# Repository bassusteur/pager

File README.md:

This project is what i think an ideal portable pager would be like, powered by a risc-v core inside the ESP32-C6 on-board, it features a pretty standard interface for a pager: except for the 
exceptionally larger LCD, it has 4 buttons for selecting and writing text.  
Communication is made possible through various methods such as zigbee or wifi, the neat part is the Serial port which could allow for fun tinkering with computers and embedded devices.
Portability wise i have added an 18650 battery pack and all the circuitry necessary to make this an off-grid device.

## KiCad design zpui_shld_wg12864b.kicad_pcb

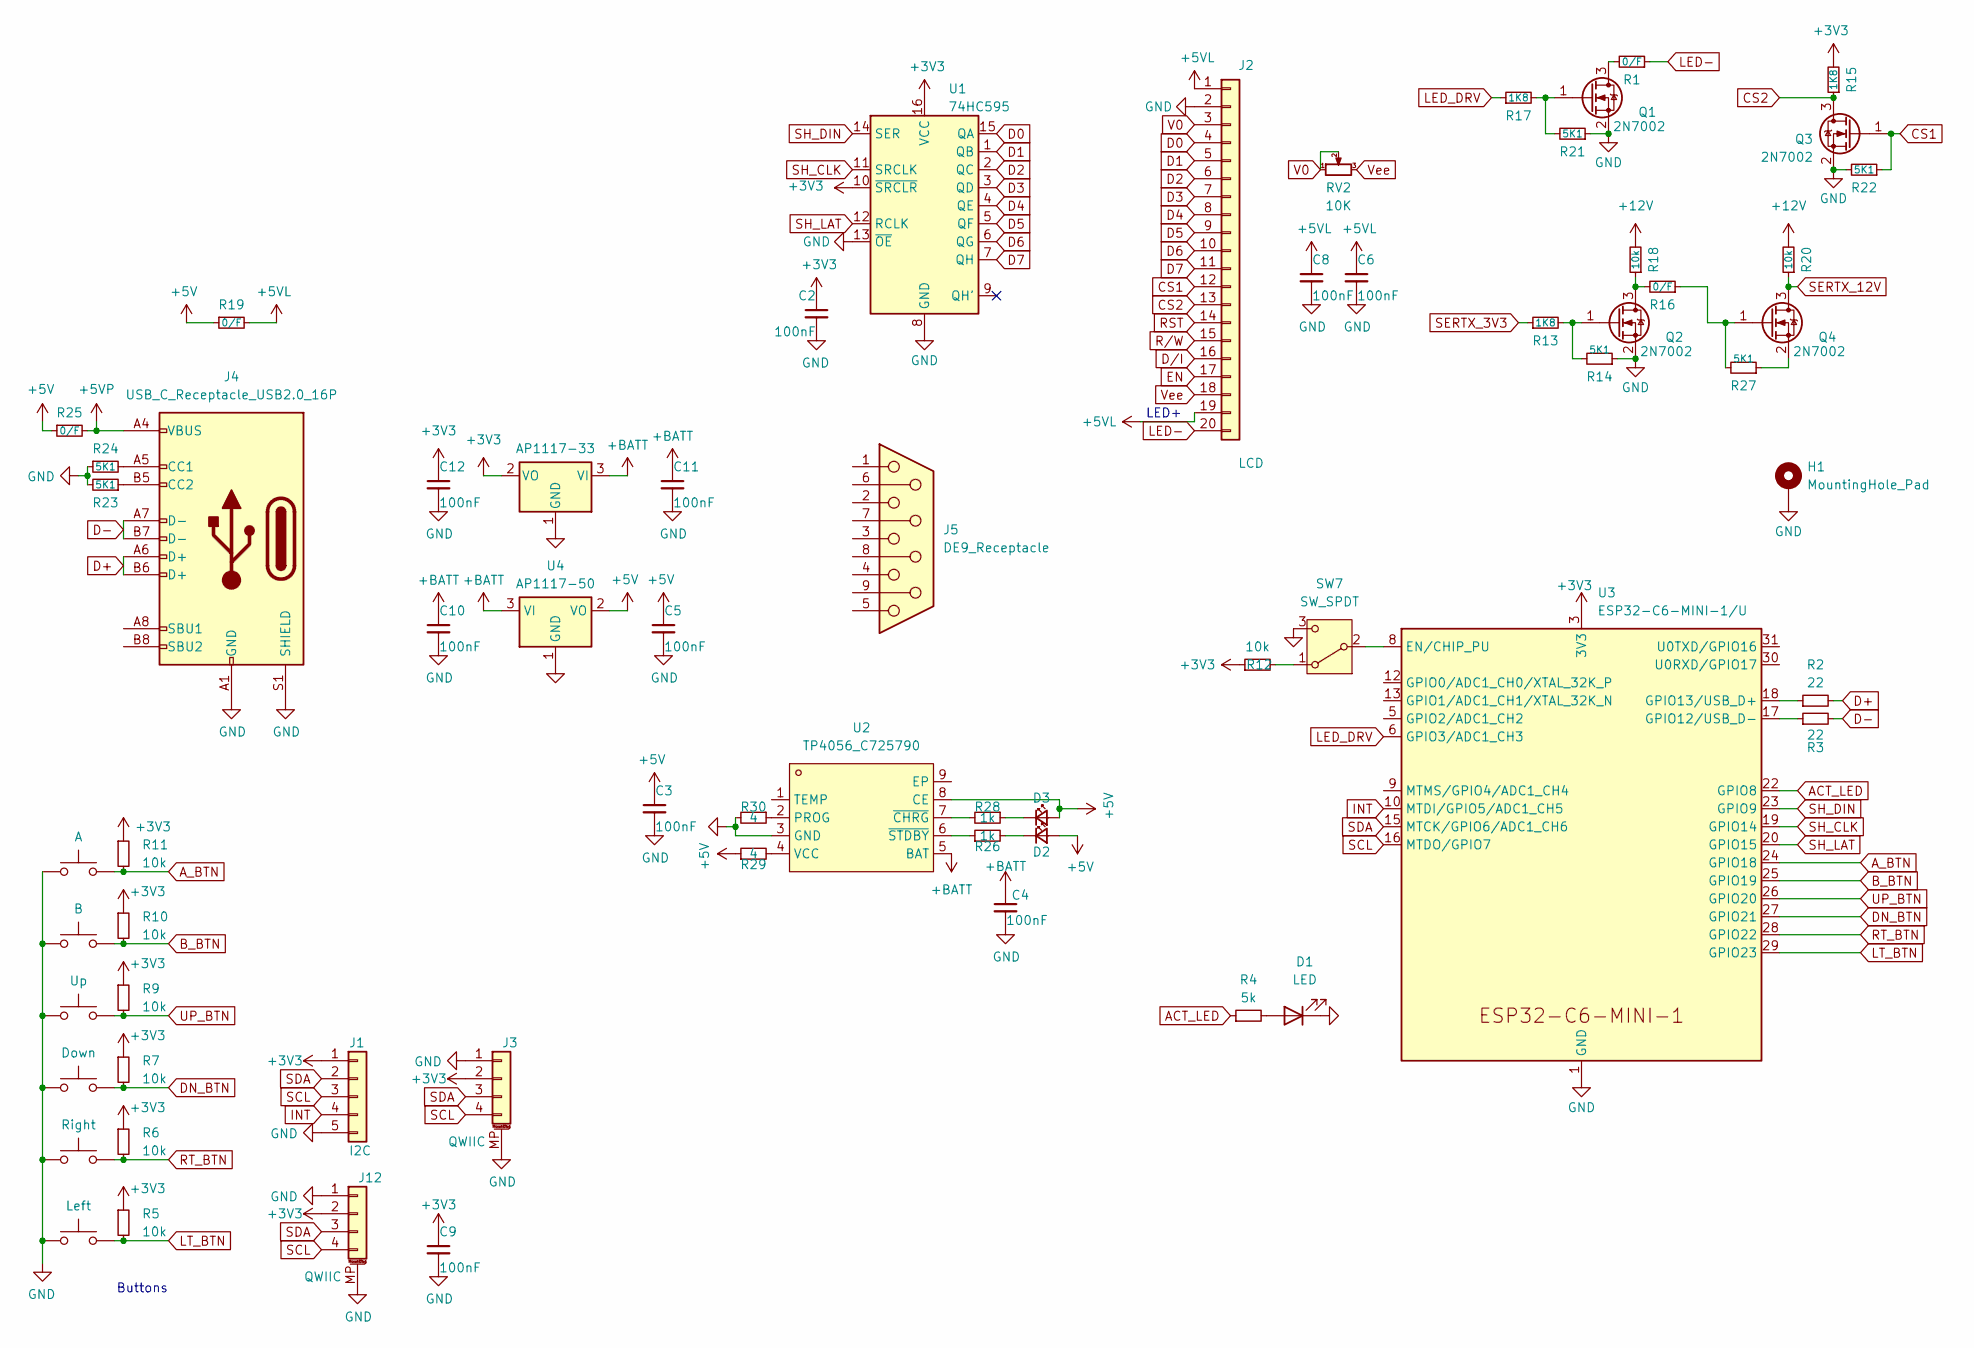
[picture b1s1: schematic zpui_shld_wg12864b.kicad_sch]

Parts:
C2, C3, C4, C5, C6, C8, C9, C10, C11, C12: 100nF; C_0603_1608Metric
D1: LED; LED_0603_1608Metric
D2, D3: LED_Small; LED_0603_1608Metric
H1: MountingHole_Pad; MountingHole_3mm_Pad
J1: I2C; PinHeader_1x05_P2.54mm_Vertical
J2: LCD; PinHeader_1x20_P2.54mm_Vertical
J3, J12: QWIIC; JST_SH_SM04B-SRSS-TB_1x04-1MP_P1.00mm_Horizontal
J4: USB_C_Receptacle_USB2.0_16P; USB_C_Receptacle_HRO_TYPE-C-31-M-12
J5: DE9_Receptacle
Q1, Q2, Q3, Q4: 2N7002; SOT-23
R1, R16, R19, R25: 0/F; R_0805_2012Metric
R2, R3: 22; R_0603_1608Metric
R4: 5k; R_0603_1608Metric
R5, R6, R7, R9, R10, R11, R18, R20: 10k; R_0603_1608Metric
R12: 10k
R13, R15, R17: 1K8; R_0603_1608Metric
R14, R21, R22, R23, R24, R27: 5K1; R_0603_1608Metric
R26, R28: 1k; R_0603_1608Metric
R29, R30: 4; R_0603_1608Metric
RV2: 10K; Potentiometer_Bourns_3314J_Vertical
SW1: A; SW_SPST_PTS645; LCSC Part # C285456
SW2: B; SW_SPST_PTS645; mpn REQUIRED https://www.lcsc.com/product-d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; LCSC Part # C285456
SW3: Up; SW_SPST_PTS645; mpn REQUIRED https://www.lcsc.com/product-d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; LCSC Part # C285456
SW4: Down; SW_SPST_PTS645; mpn REQUIRED https://www.lcsc.com/product-d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; LCSC Part # C285456
SW5: Right; SW_SPST_PTS645; mpn REQUIRED https://www.lcsc.com/product-d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; LCSC Part # C285456
SW6: Left; SW_SPST_PTS645; mpn REQUIRED https://www.lcsc.com/product-d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; LCSC Part # C285456
SW7: SW_SPDT
U1: 74HC595; SO-16_3.9x9.9mm_P1.27mm
U2: TP4056_C725790; ESOP-8_L4.9-W3.9-P1.27-LS6.0-BL-EP; LCSC Part C725790
U3: ESP32-C6-MINI-1/U; ESP32-C6-MINI-1
U4: AP1117-50; SOT-223-3_TabPin2
U5: AP1117-33; SOT-223-3_TabPin2

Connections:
+3V3: C2.1, C9.1, C12.1, J1.1, J3.2, J12.2, R5.1, R6.1, R7.1, R9.1, R10.1, R11.1, R12.1, R15.2, U1.10 (~SRCLR), U1.16 (VCC), U3.3 (3V3), U5.2 (VO)
+5V: C3.1, C5.1, D2.2 (A), D3.2 (A), R19.1, R25.1, R29.1, U2.8 (CE), U4.2 (VO)
+5VL: C6.1, C8.1, J2.1, J2.19, R19.2
+5VP: J4.A4 (VBUS), J4.A9 (VBUS), J4.B4 (VBUS), J4.B9 (VBUS), R25.2
+12V: R18.2, R20.2
+BATT: C4.1, C10.1, C11.1, U2.5 (BAT), U4.3 (VI), U5.3 (VI)
ACT_LED: R4.1, U3.22 (GPIO8)
A_BTN: R11.2, SW1.1, U3.24 (GPIO18)
B_BTN: R10.2, SW2.1, U3.25 (GPIO19)
CS1: J2.12, Q3.1 (G), R22.1
CS2: J2.13, Q3.3 (D), R15.1
D0: J2.4, U1.15 (QA)
D1: J2.5, U1.1 (QB)
D2: J2.6, U1.2 (QC)
D3: J2.7, U1.3 (QD)
D4: J2.8, U1.4 (QE)
D5: J2.9, U1.5 (QF)
D6: J2.10, U1.6 (QG)
D7: J2.11, U1.7 (QH)
D+: J4.A6 (D+), J4.B6 (D+), R2.2
D-: J4.A7 (D-), J4.B7 (D-), R3.2
DN_BTN: R7.2, SW4.1, U3.27 (GPIO21)
D/I: J2.16
EN: J2.17
GND: C2.2, C3.2, C4.2, C5.2, C6.2, C8.2, C9.2, C10.2, C11.2, C12.2, D1.1 (K), H1.1, J1.5, J2.2, J3.1, J3.MP (MountPin), J4.A1 (GND), J4.A12 (GND), J4.B1 (GND), J4.B12 (GND), J4.S1 (SHIELD), J12.1, J12.MP (MountPin), Q1.2 (S), Q2.2 (S), Q3.2 (S), R14.1, R21.1, R22.2, R23.2, R24.1, R30.2, SW1.2, SW2.2, SW3.2, SW4.2, SW5.2, SW6.2, SW7.3 (C), U1.8 (GND), U1.13 (~OE), U2.3 (GND), U3.1 (GND), U3.2 (GND), U3.11 (GND), U3.14 (GND), U3.36 (GND), U3.37 (GND), U3.38 (GND), U3.39 (GND), U3.40 (GND), U3.41 (GND), U3.42 (GND), U3.43 (GND), U3.44 (GND), U3.45 (GND), U3.46 (GND), U3.47 (GND), U3.48 (GND), U3.49 (GND), U3.50 (GND), U3.51 (GND), U3.52 (GND), U3.53 (GND), U4.1 (GND), U5.1 (GND)
INT: J1.4, U3.10 (MTDI/GPIO5/ADC1_CH5)
LED-: J2.20, R1.1
LED_DRV: R17.1, U3.6 (GPIO3/ADC1_CH3)
LT_BTN: R5.2, SW6.1, U3.29 (GPIO23)
unnamed: D1.2 (A), R4.2
unnamed: D2.1 (K), R26.2
unnamed: D3.1 (K), R28.1
unnamed: J4.A5 (CC1), R24.2
unnamed: J4.B5 (CC2), R23.1
unnamed: Q1.3 (D), R1.2
unnamed: Q1.1 (G), R17.2, R21.2
unnamed: Q2.3 (D), R16.2, R18.1
unnamed: Q2.1 (G), R13.2, R14.2
unnamed: Q4.1 (G), R16.1, R27.2
unnamed: Q4.2 (S), R27.1
unnamed: R12.2, SW7.1 (A)
unnamed: SW7.2 (B), U3.8 (EN/CHIP_PU)
unnamed: R30.1, U2.2 (PROG)
unnamed: R29.2, U2.4 (VCC)
unnamed: R28.2, U2.7 (~CHRG)
unnamed: R26.1, U2.6 (~STDBY)
unnamed: R3.1, U3.17 (GPIO12/USB_D-)
unnamed: R2.1, U3.18 (GPIO13/USB_D+)
RST: J2.14
RT_BTN: R6.2, SW5.1, U3.28 (GPIO22)
R/W: J2.15
SCL: J1.3, J3.4, J12.4, U3.16 (MTDO/GPIO7)
SDA: J1.2, J3.3, J12.3, U3.15 (MTCK/GPIO6/ADC1_CH6)
SERTX_3V3: R13.1
SERTX_12V: Q4.3 (D), R20.1
SH_CLK: U1.11 (SRCLK), U3.19 (GPIO14)
SH_DIN: U1.14 (SER), U3.23 (GPIO9)
SH_LAT: U1.12 (RCLK), U3.20 (GPIO15)
UP_BTN: R9.2, SW3.1, U3.26 (GPIO20)
V0: J2.3, RV2.1, RV2.2
Vee: J2.18, RV2.3

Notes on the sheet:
Buttons
LED+

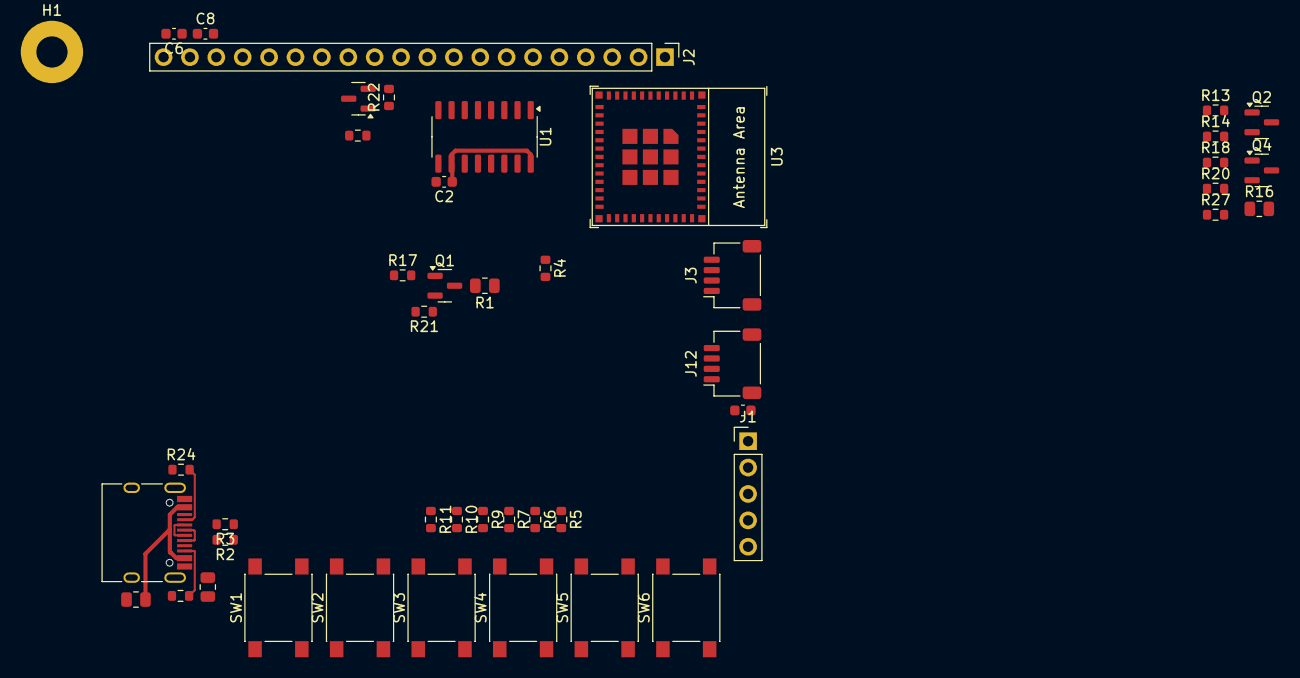
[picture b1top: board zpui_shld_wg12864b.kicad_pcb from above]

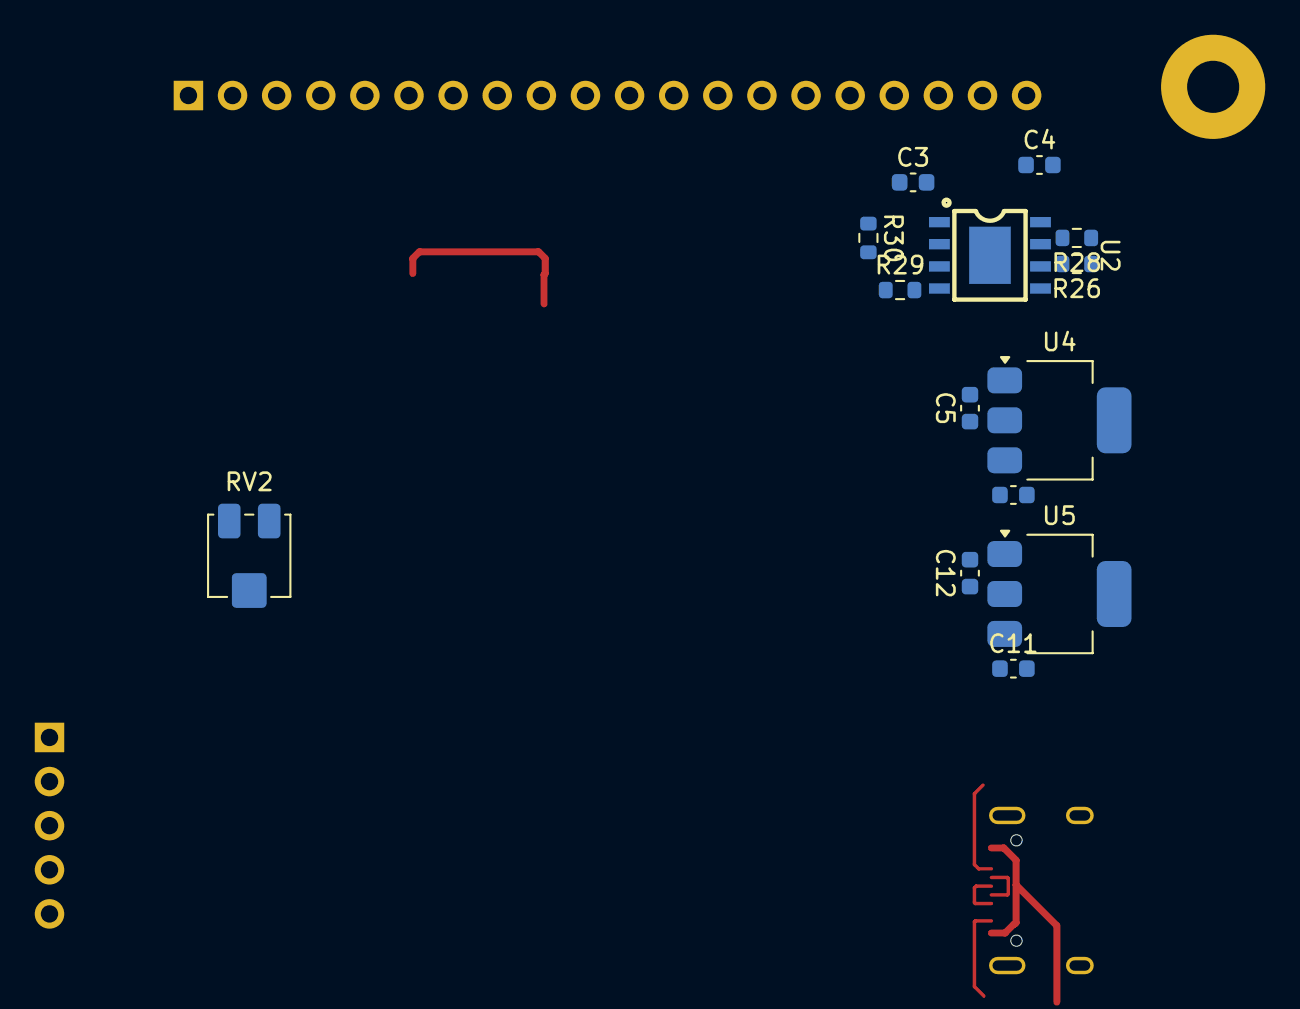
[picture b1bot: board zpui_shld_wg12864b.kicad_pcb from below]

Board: 2 copper layers, 60 parts (14 on the bottom side), 51 nets.

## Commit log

2024-07-19 add gpl
